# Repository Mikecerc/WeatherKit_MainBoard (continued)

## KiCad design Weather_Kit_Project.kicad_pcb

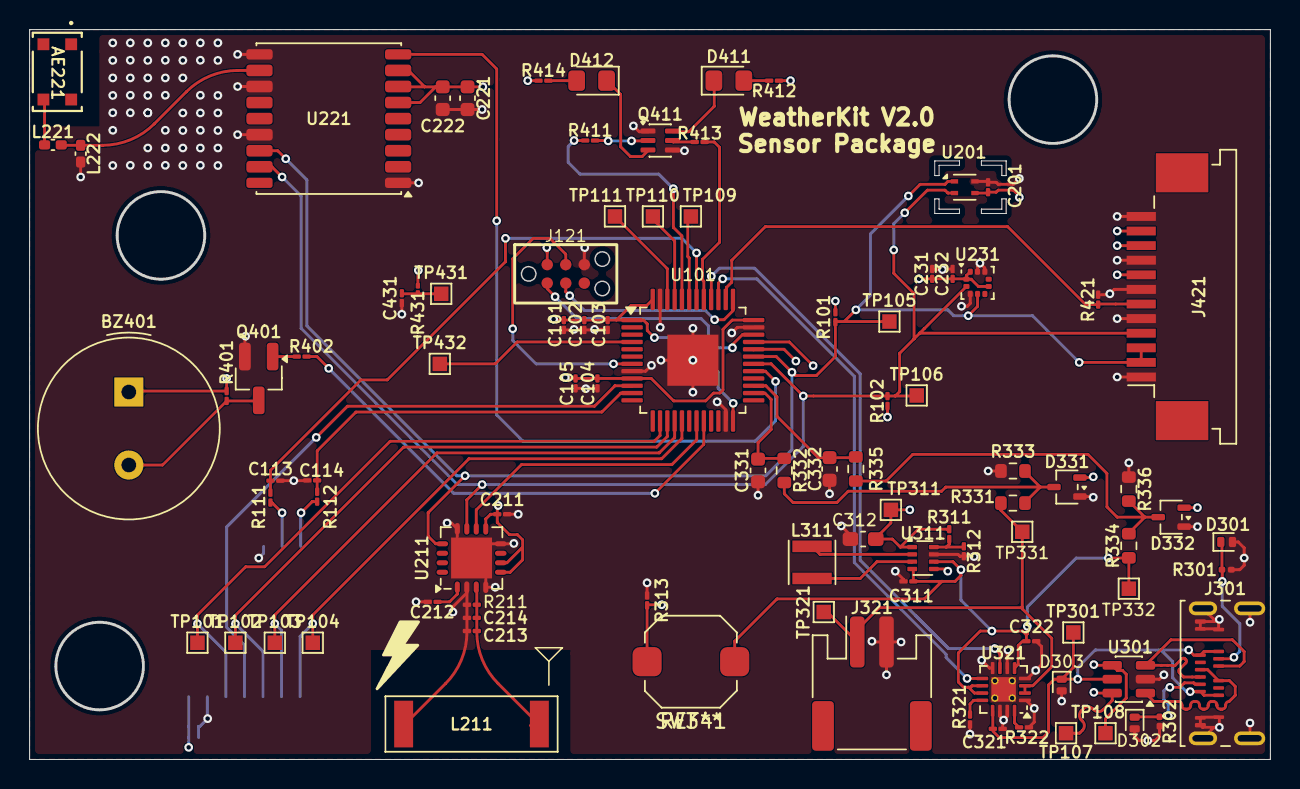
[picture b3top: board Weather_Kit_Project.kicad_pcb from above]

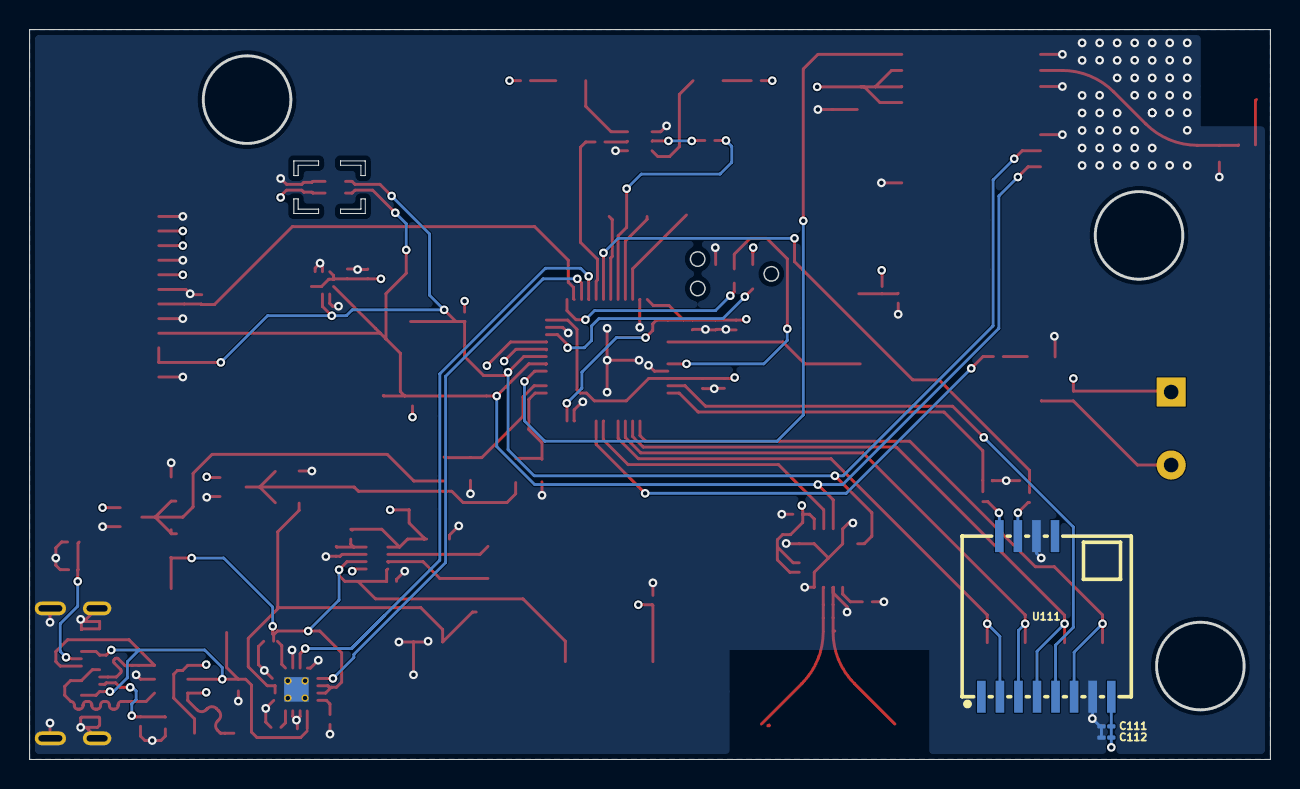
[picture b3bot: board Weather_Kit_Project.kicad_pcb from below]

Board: 4 copper layers, 85.0 x 50.0 mm, 98 parts (3 on the bottom side), 60 nets.

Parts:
AE221: 1462350001; ANT_1462350001_MOL
BZ401: Buzzer; Buzzer_TDK_PS1240P02BT_D12.2mm_H6.5mm
C101, C104, C212: 10µ; C_01005_0402Metric_Pad0.57x0.30mm_HandSolder
C102, C103, C105, C113, C114: 10n; C_01005_0402Metric_Pad0.57x0.30mm_HandSolder
C111, C201, C211, C231, C232, C431: 100n; C_01005_0402Metric_Pad0.57x0.30mm_HandSolder
C112, C321: 1µ; C_01005_0402Metric_Pad0.57x0.30mm_HandSolder
C213, C214: 470p; C_01005_0402Metric_Pad0.57x0.30mm_HandSolder
C221, C331, C332: 100n; C_0603_1608Metric
C222: 1µ; C_0603_1608Metric
C311: 22µ; C_01005_0402Metric_Pad0.57x0.30mm_HandSolder
C312: 47µ; C_0603_1608Metric_Pad1.08x0.95mm_HandSolder
C322: 4.7µ; C_01005_0402Metric_Pad0.57x0.30mm_HandSolder
D301, D302, D303: PESD5V0L1ULD; D_SOD-882D
D331, D332: BAT54SW; SOT-323_SC-70
D411: G_LED; LED_0805_2012Metric_Pad1.15x1.40mm_HandSolder
D412: R_LED; LED_0805_2012Metric_Pad1.15x1.40mm_HandSolder
J121: TC2030-IDC-NL-10; TC2030-IDC-NL
J301: USB_C_Receptacle; USB_C_Receptacle_Amphenol_124019772112A
J321: Conn_01x02; JST_PH_S2B-PH-SM4-TB_1x02-1MP_P2.00mm_Horizontal
J421: CFAL12832C0-091B-W; TE_1-84952-2_1x12-1MP_P1.0mm_Horizontal
L211: 100u; Coilcraft_MA5532-AE_RFID
L221: 5.1n; L_0402_1005Metric_Pad0.77x0.64mm_HandSolder
L222: 1.8n; L_0402_1005Metric_Pad0.77x0.64mm_HandSolder
L311: NR3015T1R5N; L_Taiyo-Yuden_NR-30xx
Q401: Q_NMOS_GSD; SOT-23_Handsoldering
Q411: Q_Dual_NMOS_S1G1D2S2G2D1; SOT-363_SC-70-6
R101, R102, R421: 4.7k; R_01005_0402Metric_Pad0.57x0.30mm_HandSolder
R111, R112, R401, R402: 1k; R_01005_0402Metric_Pad0.57x0.30mm_HandSolder
R211, R313: 10k; R_01005_0402Metric_Pad0.57x0.30mm_HandSolder
R301, R302: 5.1k; R_0201_0603Metric
R311: 511k; R_01005_0402Metric_Pad0.57x0.30mm_HandSolder
R312: 91k; R_01005_0402Metric_Pad0.57x0.30mm_HandSolder
R321: 3k; R_01005_0402Metric_Pad0.57x0.30mm_HandSolder
R322: 4.3k; R_01005_0402Metric_Pad0.57x0.30mm_HandSolder
R331, R332, R333, R334, R335, R336: 1k; R_0603_1608Metric
R411, R413: 2.2k; R_01005_0402Metric_Pad0.57x0.30mm_HandSolder
R412, R414: 300; R_01005_0402Metric_Pad0.57x0.30mm_HandSolder
R431: 10k; R_01005_0402Metric
SW341: SW_SPST; SW_Push_1TS009xxxx-xxxx-xxxx_6x6x5mm
TP101, TP102, TP103, TP104, TP105, TP106, TP107, TP108, TP109, TP110, TP111, TP301, TP311, TP321, TP331, TP332, TP431, TP432: TestPoint; TestPoint_Pad_1.0x1.0mm
U101: STM32U073C8Ux; TQFP-48-1EP_7x7mm_P0.5mm_EP3.5x3.5mm
U111: Wio-SX1262; COMM-SMD_12P-L11.6-W11.0-P1.27_114993390
U201: SHT4x; Sensirion_DFN-4_1.5x1.5mm_P0.8mm_SHT4x_NoCentralPad
U211: AS3935; MLPQ-16-1EP_4x4mm_P0.65mm_EP2.8x2.8mm
U221: MAX-M10S; ublox_MAX
U231: LPS22HHQTR; ST_HLGA-10_2x2mm_P0.5mm_LayoutBorder3x2y
U301: USBLC6-2SC6; SOT-23-6
U311: TPS631000; SOT-583-8
U321: BQ24230RGTR; VQFN-16-1EP_3x3mm_P0.5mm_EP1.68x1.68mm_ThermalVias

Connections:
+3.3V: BZ401.1 (+), C101.2, C102.2, C103.2, C104.2, C105.2, C111.1, C112.1, C201.1, C211.1, C221.1, C222.1, C231.1, C232.1, C312.2, D331.2 (K), D332.2 (K), J121.1 (VREF), J421.8, J421.10, J421.11, R101.2, R102.2, R311.2, R401.1, R412.1, R414.1, R431.2, TP311.1 (1_1), U101.1 (VBAT), U101.9 (VDDA), U101.24 (VDD), U101.36 (VDDUSB), U101.48 (VDD), U111.8 (VCC), U201.3 (VDD), U211.5 (Vdd), U211.6 (VReg), U211.9 (SI), U221.6 (V_BCKP), U221.7 (VCC_IO), U221.8 (VCC), U231.1 (Vdd_IO), U231.6 (~CS), U231.10 (VDD), U311.1 (VOUT)
/Power Network/USB_D_+: J301.A6 (D+), J301.B6 (D+), U301.3 (I/O2)
/Power Network/USB_D_-: J301.A7 (D-), J301.B7 (D-), U301.1 (I/O1)
CHRGR_PWR_OUT: C311.1, C322.1, R334.2, SW341.1 (A), TP332.1 (1_1), U311.4 (VIN), U311.6 (MODE), U321.5 (EN2), U321.10 (OUT), U321.11 (OUT)
GND: C101.1, C102.1, C103.1, C104.1, C105.1, C111.2, C112.2, C113.2, C114.2, C201.2, C211.2, C212.1, C213.1, C214.1, C221.2, C222.2, C231.2, C232.2, C311.2, C312.1, C321.2, C322.2, C331.2, C332.2, C431.1, D301.2 (A), D302.2 (A), D303.2 (A), D331.1 (A), D332.1 (A), J121.5 (GND), J301.A1 (GND), J301.A12 (GND), J301.B1 (GND), J301.B12 (GND), J301.SH (SHIELD), J321.2, J421.1, J421.5, J421.7, J421.9, J421.12, L211.1, L222.2, Q401.2 (S), Q411.1 (S), Q411.4 (S), R211.1, R301.2, R302.2, R312.1, R313.1, R321.1, R322.2, R333.1, R336.1, R421.2, U101.8 (VSSA), U101.23 (VSS), U101.35 (VSS), U101.47 (VSS), U101.49 (VSS), U111.7 (GND), U111.10 (GND), U201.4 (VSS), U211.2 (IN-), U211.4 (GND), U211.8 (CS), U211.12 (MISO), U211.17 (GNDPAD), U221.1 (GND), U221.10 (GND), U221.12 (GND), U221.15 (VIO_SEL), U231.3 (GND), U231.8 (GND), U231.9 (GND), U301.2 (GND), U311.7 (GND), U321.1 (TS), U321.4 (CE), U321.6 (EN1), U321.8 (VSS), U321.14 (TMR), U321.15 (TD), U321.17 (VSS)
I2C_CLK: J421.4, R102.1, TP106.1 (1_1), U101.30 (PA9), U201.2 (SCL), U211.11 (SCL), U221.17 (SCL), U231.2 (SCL)
I2C_DATA: J421.2, J421.3, R101.1, TP105.1 (1_1), U101.31 (PA10), U201.1 (SDA), U211.13 (MOSI/SDA), U221.16 (SDA), U231.4 (SDA)
MCU_AI_BATTERY_V: C331.1, R332.2, U101.26 (PB13)
MCU_AI_VOUT: C332.1, R335.2, U101.27 (PB14)
MCU_DI_CHRGR_CHG: U101.39 (PB3), U321.9 (CHG)
MCU_DI_CHRGR_PGOOD: U101.40 (PB4), U321.7 (PGOOD)
MCU_DI_JTAG_SWCLK: J121.4 (SWCLK), U101.37 (PA14)
MCU_DI_JTAG_SWDIO: J121.2 (SWDIO), U101.34 (PA13)
MCU_DI_JTAG_nRST: J121.3 (nRESET), U101.7 (PF2)
MCU_DI_LORA_BUSY: C113.1, R111.2, U101.42 (PB6)
MCU_DI_LORA_DIO1: C114.1, R112.2, U101.11 (PA1)
MCU_DI_LTNG_IRQ: U101.19 (PB1), U211.10 (IRQ)
MCU_DI_NAVBTN: TP432.1 (1_1), U101.4 (PC15)
MCU_DO_BZR_EN: R402.1, U101.20 (PB2)
MCU_DO_GLED: R411.2, U101.44 (PF3)
MCU_DO_GPS_RST: U101.29 (PA8), U221.9 (~RESET)
MCU_DO_LORA_RST: U101.10 (PA0), U111.5 (~NRST)
MCU_DO_OLED_RST: J421.6, R421.1, U101.38 (PA15)
MCU_DO_RLED: R413.2, U101.41 (PB5)
unnamed: AE221.3 (3_3), L221.2
unnamed: BZ401.2 (-), Q401.3 (D), R401.2
unnamed: C431.2, R431.1, TP431.1 (1_1)
unnamed: D301.1 (K), J301.B5 (CC2), R301.1
unnamed: D302.1 (K), J301.A5 (CC1), R302.1
unnamed: D331.3 (COM), R331.1, R332.1, R333.2
unnamed: D332.3 (COM), R334.1, R335.1, R336.2
unnamed: D411.2 (A), R412.2
unnamed: D411.1 (K), Q411.6 (D)
unnamed: D412.2 (A), R414.2
unnamed: D412.1 (K), Q411.3 (D)
unnamed: Q401.1 (G), R402.2
unnamed: Q411.2 (G), R411.1
unnamed: Q411.5 (G), R413.1
unnamed: R313.2, SW341.2 (B), U311.5 (EN)
unnamed: TP109.1 (1_1), U101.43 (PB7)
unnamed: TP110.1 (1_1), U101.45 (PB8)
unnamed: TP111.1 (1_1), U101.46 (PB9)
unnamed: R111.1, U111.11 (BUSY)
unnamed: R112.1, U111.12 (DIO1)
unnamed: C212.2, U211.1 (ACG)
unnamed: C213.2, C214.2, L211.2, R211.2, U211.3 (IN+)
unnamed: L221.1, L222.1, U221.11 (RF_IN)
unnamed: R311.1, R312.2, U311.8 (FB)
unnamed: L311.1, U311.3 (LX1)
unnamed: L311.2, U311.2 (LX2)
unnamed: R321.2, U321.12 (ILIM)
unnamed: R322.1, U321.16 (ISET)
SPI_CLK: TP102.1 (1_1), U101.15 (PA5), U111.4 (SCK)
SPI_MISO: TP104.1 (1_1), U101.17 (PA7), U111.2 (MISO)
SPI_MOSI: TP103.1 (1_1), U101.16 (PA6), U111.3 (MOSI)
SPI_NSS: TP101.1 (1_1), U101.14 (PA4), U111.6 (~NSS)
USB_D_N: TP107.1 (1_1), U101.32 (PA11), U301.6 (I/O1)
USB_D_P: TP108.1 (1_1), U101.33 (PA12), U301.4 (I/O2)
VBATT: J321.1, R331.2, TP321.1 (1_1), TP331.1 (1_1), U321.2 (BAT), U321.3 (BAT)
VBUS: C321.1, D303.1 (K), J301.A4 (VBUS), J301.A9 (VBUS), J301.B4 (VBUS), J301.B9 (VBUS), TP301.1 (1_1), U301.5 (VBUS), U321.13 (IN)

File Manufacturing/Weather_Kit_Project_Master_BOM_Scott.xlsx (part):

SENSOR STATION |  |  |  |  |  |  |  |  | BASE STATION
Reference | Qty Per Board | Total Qty | Value | PPT | Total Price | Footprint | Supplier Link |  | Reference | Qty Per Board | Total Qty | Value | PPT | Total Price | Footprint | Supplier Link
AE221 | 1 | 6 | 1462350001 | 1.06 | 6.36 | Library:ANT_1462350001_MOL | https://www.digikey.com/en/products/detail/molex/1462350001/6159253 |  | D101 | 1 | 1 | SS34 | 0.16 | 0.16 | Diode_SMD:D_SMA | https://www.digikey.com/en/products/detail/shenzhen-slkormic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
BZ401 | 1 | 10 | Buzzer | 0.54600000000000004 | 5.4600000000000009 | Buzzer_Beeper:Buzzer_TDK_PS1240P02BT_D12.2mm_H6.5mm | https://www.digikey.com/en/products/detail/tdk/PS1240P02BT/9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 |  | J121 | 1 | 1 | Waveshare 5" DSI Display | 49.99 | 49.99 |  | Amazon.com: Waveshare 5inch DSI Capacitive Touch Display, Compatible with Raspb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
C101,C104,C212 | 3 | 24 | 10Âµ | 9.5000000000000001E-2 | 2.2800000000000002 | Capacitor_SMD:C_01005_0402Metric_Pad0.57x0.30mm_HandSolder | https://www.digikey.com/en/products/detail/murata-electronic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 |  | R211 | 1 | 1 | 2k | 0.1 | 0.1 | Resistor_SMD:R_0201_0603Metric_Pad0.64x0.40mm_HandSolder | https://www.digikey.com/en/products/detail/stackpole-electro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
C102,C103,C105,C113,C114 | 5 | 50 | 10n | 2.58E-2 | 1.29 | Capacitor_SMD:C_01005_0402Metric_Pad0.57x0.30mm_HandSolder | https://www.digikey.com/en/products/detail/cal-chip-electron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 |  | R221 | 1 | 1 | 90k | 0.14000000000000001 | 0.14000000000000001 | Resistor_SMD:R_01005_0402Metric_Pad0.57x0.30mm_HandSolder | https://www.digikey.com/en/products/detail/yageo/RT1206DRE07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
C111,C201,C211,C231,C232,C431 | 6 | 54 | 100n | 1.6400000000000001E-2 | 0.88560000000000005 | Capacitor_SMD:C_01005_0402Metric_Pad0.57x0.30mm_HandSolder | https://www.digikey.com/en/products/detail/murata-electronic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 |  | U102 | 1 | 1 | ESP32-P4-PICO-Dev-Board | 18.989999999999998 | 18.989999999999998 | Weather_Kit:ESP32-P4-Pico | Amazon.com: ESP32-P4-Pico Development Board Based On ESP32-P4,32MB PSRAM,32MB N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
C112,C321 | 2 | 20 | 1Âµ | 6.4000000000000001E-2 | 1.28 | Capacitor_SMD:C_01005_0402Metric_Pad0.57x0.30mm_HandSolder | https://www.digikey.com/en/products/detail/tdk/C1005X6S1C105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 |  | Batt | 1 | 1 | 10000mAh | 18.989999999999998 | 18.989999999999998 |  | https://www.amazon.com/JLJLUP-Rechargeable-Protective-Insula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
C213,C214 | 2 | 14 | 470p | 1.4E-2 | 0.19600000000000001 | Capacitor_SMD:C_01005_0402Metric_Pad0.57x0.30mm_HandSolder | https://www.digikey.com/en/products/detail/murata-electronic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 |  | PCB |  |  |  |  | 43.98
C221,C331,C332 | 3 | 20 | 100n | 7.6999999999999999E-2 | 1.54 | Capacitor_SMD:C_0603_1608Metric | https://www.digikey.com/en/products/detail/murata-electronic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
C222 | 1 | 10 | 1Âµ | 0.09 | 0.89999999999999991 | Capacitor_SMD:C_0603_1608Metric | https://www.digikey.com/en/products/detail/murata-electronic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 |  |  |  |  | Base Station Total |  | 132.19
C311 | 1 | 10 | 22Âµ | 0.36699999999999999 | 3.67 | Capacitor_SMD:C_01005_0402Metric_Pad0.57x0.30mm_HandSolder | https://www.digikey.com/en/products/detail/samsung-electro-m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
C312 | 1 | 10 | 47Âµ | 0.41 | 4.0999999999999996 | Capacitor_SMD:C_0603_1608Metric_Pad1.08x0.95mm_HandSolder | https://www.digikey.com/en/products/detail/murata-electronic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
C322 | 1 | 20 | 4.7Âµ | 0.12 | 2.4 | Capacitor_SMD:C_01005_0402Metric_Pad0.57x0.30mm_HandSolder | https://www.digikey.com/en/products/detail/murata-electronic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
D301,D302,D303 | 3 | 30 | PESD5V0L1ULD | 0.183 | 5.49 | Diode_SMD:D_SOD-882D | https://www.digikey.com/en/products/detail/evvo/PESD5V0L1UL/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
D331,D332 | 2 | 20 | BAT54SW | 0.108 | 2.16 | Package_TO_SOT_SMD:SOT-323_SC-70 | https://www.digikey.com/en/products/detail/diotec-semiconduc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
D411 | 1 | 10 | G_LED | 0.104 | 1.04 | LED_SMD:LED_0805_2012Metric_Pad1.15x1.40mm_HandSolder | https://www.digikey.com/en/products/detail/liteon/LTST-C171G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
D412 | 1 | 10 | R_LED | 0.109 | 1.0900000000000001 | LED_SMD:LED_0805_2012Metric_Pad1.15x1.40mm_HandSolder | https://www.digikey.com/en/products/detail/liteon/LTST-C171K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
J121 | 1 | N/A | TC2030-IDC-NL-10 |  | 0 | Library:TC2030-IDC-NL
J301 | 1 | 5 | USB_C_Receptacle | 1.9990000000000001 | 9.995000000000001 | Connector_USB:USB_C_Receptacle_Amphenol_124019772112A | https://www.digikey.com/en/products/detail/amphenol-cs-comme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
J321 | 1 | 10 | Conn_01x02 | 0.41699999999999998 | 4.17 | Connector_JST:JST_PH_S2B-PH-SM4-TB_1x02-1MP_P2.00mm_Horizontal | https://www.digikey.com/en/products/detail/jst-sales-america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
J421 | 1 | 5 | CFAL12832C0-091B-W | 5.81 | 29.049999999999997 | Connector_FFC-FPC:TE_1-84952-2_1x12-1MP_P1.0mm_Horizontal | https://www.crystalfontz.com/product/cfal12832c0091bw-small-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
L211 | 1 | 2 | 100u | 1.36 | 2.72 | RF_Antenna:Coilcraft_MA5532-AE_RFID | https://www.coilcraft.com/en-us/products/rf/rfid-transponder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
L221 | 1 | 10 | 5.1n | 3.1E-2 | 0.31 | Inductor_SMD:L_0402_1005Metric_Pad0.77x0.64mm_HandSolder | https://www.digikey.com/en/products/detail/johanson-technolo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
L222 | 1 | 10 | 1.8n | 0.03 | 0.3 | Inductor_SMD:L_0402_1005Metric_Pad0.77x0.64mm_HandSolder | https://www.digikey.com/en/products/detail/johanson-technolo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
L311 | 1 | 10 | LSXND3030QKT1R5NNG | 0.182 | 1.8199999999999998 | Inductor_SMD:L_Taiyo-Yuden_NR-30xx | https://www.digikey.com/en/products/detail/taiyo-yuden/LSXND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
Q401 | 1 | 10 | Q_NMOS_GSD | 0.42499999999999999 | 4.25 | Package_TO_SOT_SMD:SOT-23_Handsoldering | https://www.digikey.com/en/products/detail/umw/FDN335N/16705940
Q411 | 1 | 10 | Q_Dual_NMOS_S1G1D2S2G2D1 | 0.18 | 1.7999999999999998 | Package_TO_SOT_SMD:SOT-363_SC-70-6 | https://www.digikey.com/en/products/detail/nexperia-usa-inc/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
R101,R102,R421 | 3 | 30 | 4.7k | 0.09 | 2.6999999999999997 | Resistor_SMD:R_01005_0402Metric_Pad0.57x0.30mm_HandSolder | https://www.digikey.com/en/products/detail/yageo/RC0100JR-07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
R111,R112,R401,R402 | 4 | 50 | 1k | 2.8799999999999999E-2 | 1.44 | Resistor_SMD:R_01005_0402Metric_Pad0.57x0.30mm_HandSolder | https://www.digikey.com/en/products/detail/bourns-inc/CR0100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
R211,R313 | 2 | 34 | 10k | 3.5200000000000002E-2 | 1.1968000000000001 | Resistor_SMD:R_01005_0402Metric_Pad0.57x0.30mm_HandSolder | https://www.digikey.com/en/products/detail/bourns-inc/CR0100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
R301,R302 | 2 | 20 | 5.1k | 2.9000000000000001E-2 | 0.58000000000000007 | Resistor_SMD:R_0201_0603Metric | https://www.digikey.com/en/products/detail/delta-electronics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
R311 | 1 | 10 | 511k | 4.2999999999999997E-2 | 0.42999999999999994 | Resistor_SMD:R_01005_0402Metric_Pad0.57x0.30mm_HandSolder | https://www.digikey.com/en/products/detail/vishay-dale/CRCW0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
R312 | 1 | 10 | 91k | 0.14000000000000001 | 1.4000000000000001 | Resistor_SMD:R_01005_0402Metric_Pad0.57x0.30mm_HandSolder | https://www.digikey.com/en/products/detail/yageo/RC0100FR-07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
R321 | 1 | 10 | 3k | 3.5000000000000003E-2 | 0.35000000000000003 | Resistor_SMD:R_01005_0402Metric_Pad0.57x0.30mm_HandSolder | https://www.digikey.com/en/products/detail/delta-electronics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
R322 | 1 | 10 | 4.3k | 0.09 | 0.89999999999999991 | Resistor_SMD:R_01005_0402Metric_Pad0.57x0.30mm_HandSolder | https://www.digikey.com/en/products/detail/yageo/RC0100JR-07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
R331,R332,R333,R334,R335,R336 | 6 | 60 | 1k | 2.3599999999999999E-2 | 1.4159999999999999 | Resistor_SMD:R_0603_1608Metric | https://www.digikey.com/en/products/detail/panasonic-industr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
R411,R413 | 2 | 20 | 2.2k | 0.03 | 0.6 | Resistor_SMD:R_01005_0402Metric_Pad0.57x0.30mm_HandSolder | https://www.digikey.com/en/products/detail/delta-electronics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
R412,R414 | 2 | 20 | 300 | 3.5000000000000003E-2 | 0.70000000000000007 | Resistor_SMD:R_01005_0402Metric_Pad0.57x0.30mm_HandSolder | https://www.digikey.com/en/products/detail/delta-electronics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 |  | Current Total: |  |  |  | 555.47939999999994
SW341 | 1 | 10 | SW_SPST | 1.9 | 19 |  | https://www.amazon.com/dp/B0FMF8P2XM
SW431 | 1 | 10 | SW_Push | 0.7 | 7 |  | https://www.amazon.com/Gebildet-3V-6V-12V-24V-230V-Prewired-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
TP101,TP102,TP103,TP104,TP105,TP106,TP107,TP108,TP109,TP110,TP111,TP301,TP311,T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 | 18 | N/A | TestPoint |  | 0 | TestPoint:TestPoint_Pad_1.0x1.0mm
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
